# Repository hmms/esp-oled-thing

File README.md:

# esp-oled-thing
yet another esp8266 project

PCB designed in eagle 6.2.0.

gerbers in .zip file sent to OSH park 

this is still a work in progress.

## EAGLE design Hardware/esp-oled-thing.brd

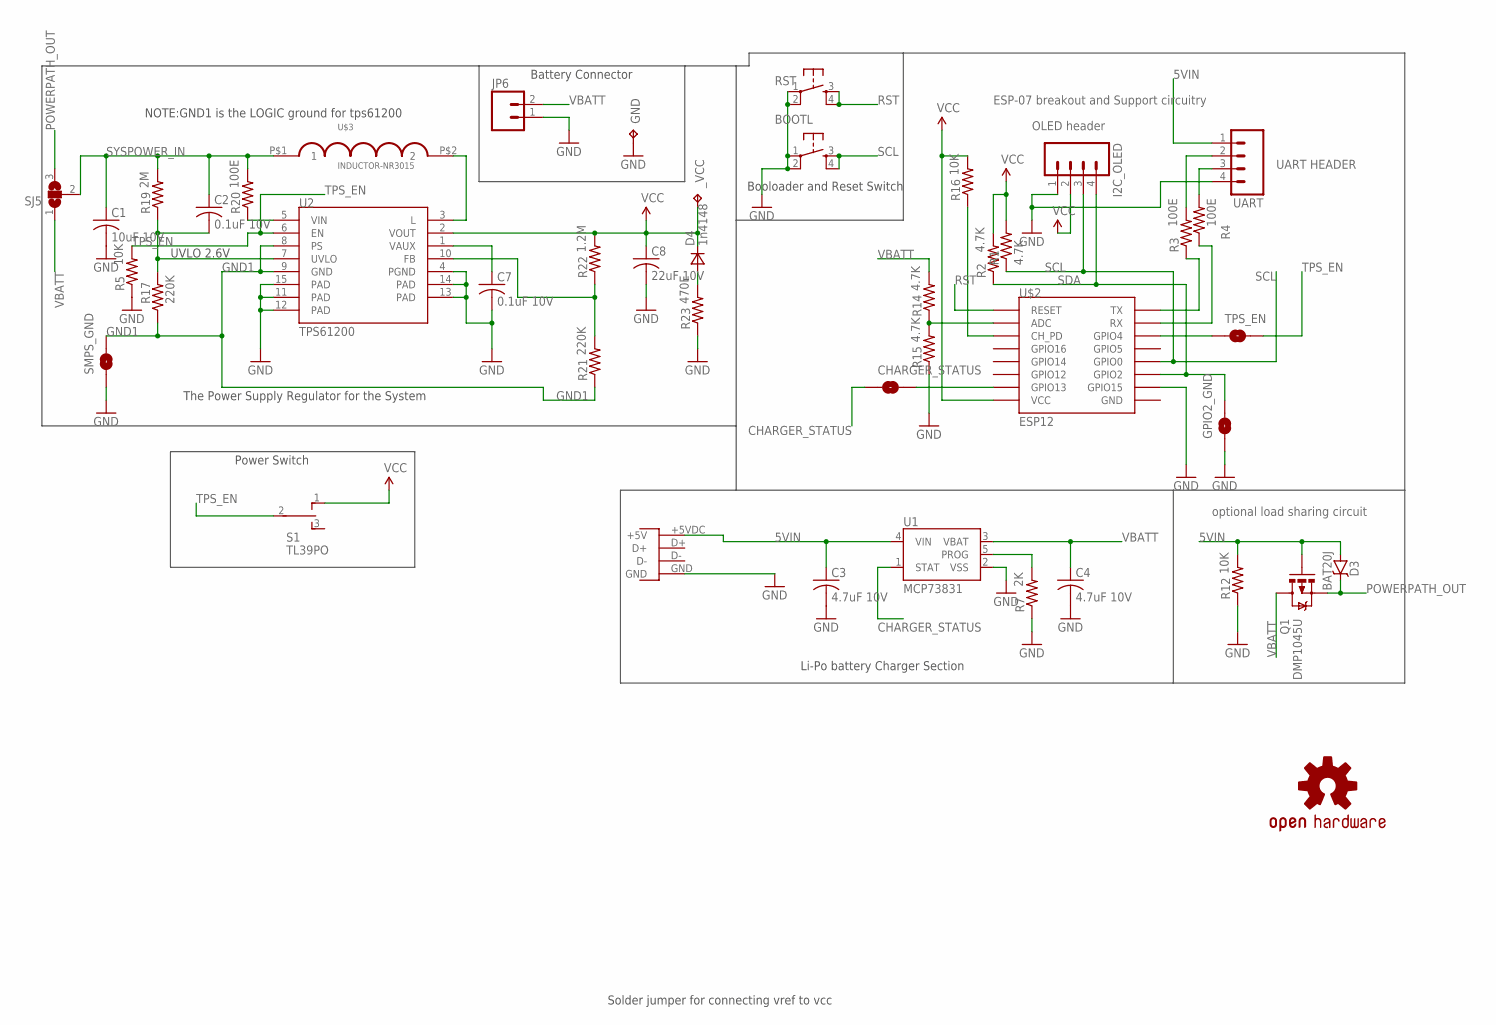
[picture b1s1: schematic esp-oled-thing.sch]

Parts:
BOOTL: TAC_SWITCHSMD; TACTILE_SWITCH_SMD
C1: 10uF 10V; C0805
C2, C7: 0.1uF 10V; C0805
C3, C4: 4.7uF 10V; C0805
C8: 22uF 10V; C0805
CHARGER_STATUS: SOLDERJUMPERNO; SJ_2S-NO
D3: BAT20J; SOD-323
D4: 1n4148; SOD323
GND: TPTP10R; TP10R
GPIO2_GND: SOLDERJUMPERNO; SJ_2S-NO
I2C_OLED: M04PTH; 1X04
JP6: M02JST-PTH-2; JST-2-PTH
Q1: DMP1045U; SOT23-3
R1, R2, R14, R15: 4.7K; M0805
R3, R4, R20: 100E; M0805
R5, R12, R16: 10K; M0805
R7: 2K; M0805
R17, R21: 220K; M0805
R19: 2M; M0805
R22: 1.2M; M0805
R23: 470E; M0805
RST: TAC_SWITCHSMD; TACTILE_SWITCH_SMD
S1: TL39PO; TL3XPO
SJ5: SJ2W; SJ_2
SMPS_GND: SOLDERJUMPERNO; SJ_2S-NO
TPS_EN: SOLDERJUMPERNO; SJ_2S-NO
U1: MCP73831; SOT23-5
U2: TPS61200; QFN-10_PAD
U$1: OSHW-LOGOS; OSHW-LOGO-S
U$2: ESP12
U$3: INDUCTOR-NR3015
U$4: MICROUSB-MIDMOUNT; MICROUSB-MIDMOUNT-MOLEX
UART: M04LONGPADS; 1X04_LONGPADS
_VCC: TPTP10R; TP10R

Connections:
5VIN: C3.1, D3.A, Q1.1 (G), R12.2, U1.4 (VIN), U$4.+5VDC (+5V), UART.1
CHARGER_STATUS: CHARGER_STATUS.1, U1.1 (STAT)
FB: R21.2, R22.1, U2.10 (FB)
GND: BOOTL.1, BOOTL.2, C1.2, C3.2, C4.2, C7.2, C8.2, GND.TP, GPIO2_GND.1, I2C_OLED.1, JP6.1, R5.1, R7.1, R12.1, R15.1, R23.1, RST.1, RST.2, SMPS_GND.1, U1.2 (VSS), U2.4 (PGND), U2.11 (PAD), U2.12 (PAD), U2.13 (PAD), U2.14 (PAD), U2.15 (PAD), U$2.GPIO15, U$4.GND, UART.4
GND1: R17.1, R21.1, SMPS_GND.2, U2.8 (PS), U2.9 (GND)
unnamed: CHARGER_STATUS.2, U$2.GPIO13
unnamed: R14.1, R15.2, U$2.ADC
unnamed: R16.1, U$2.CH_PD
unnamed: R3.2, UART.2
unnamed: TPS_EN.1, U$2.GPIO4
unnamed: R4.2, UART.3
unnamed: R7.2, U1.5 (PROG)
unnamed: U2.3 (L), U$3.P$2 (2)
unnamed: C7.1, U2.1 (VAUX)
unnamed: R3.1, U$2.TX
unnamed: R4.1, U$2.RX
unnamed: D4.2 (A), R23.2
POWERPATH_OUT: D3.C, Q1.2 (S), SJ5.3
RST: RST.3, RST.4, U$2.RESET
SCL: BOOTL.3, BOOTL.4, I2C_OLED.3, R1.1, U$2.GPIO0
SDA: GPIO2_GND.2, I2C_OLED.4, R2.1, U$2.GPIO2
SYSPOWER_IN: C1.1, C2.1, R19.2, R20.2, SJ5.2, U$3.P$1 (1)
TPS_EN: R5.2, S1.2, TPS_EN.2, U2.6 (EN)
UVLO: C2.2, R17.2, R19.1, U2.7 (UVLO)
VBATT: C4.1, JP6.2, Q1.3 (D), R14.2, SJ5.1, U1.3 (VBAT)
VCC: C8.1, D4.1 (C), I2C_OLED.2, R1.2, R2.2, R16.2, R22.2, S1.1 (O), U2.2 (VOUT), U$2.VCC, _VCC.TP
VIN: R20.1, U2.5 (VIN)

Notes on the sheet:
OLED header
UART HEADER
Booloader and Reset Switch
ESP-07 breakout and Support circuitry
UVLO 2.6V
NOTE:GND1 is the LOGIC ground for tps61200
Li-Po battery Charger Section
The Power Supply Regulator for the System
Solder jumper for connecting vref to vcc
optional load sharing circuit
Power Switch
Battery Connector

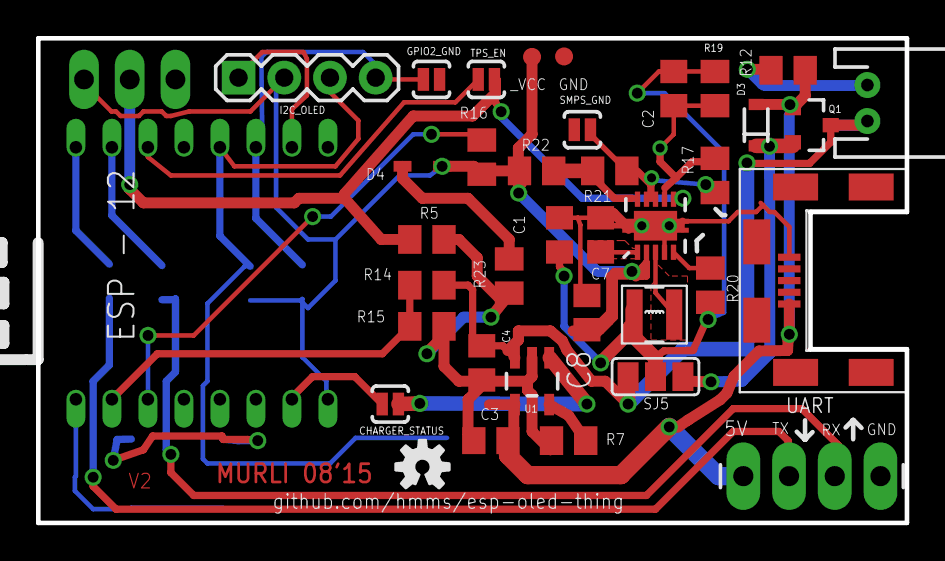
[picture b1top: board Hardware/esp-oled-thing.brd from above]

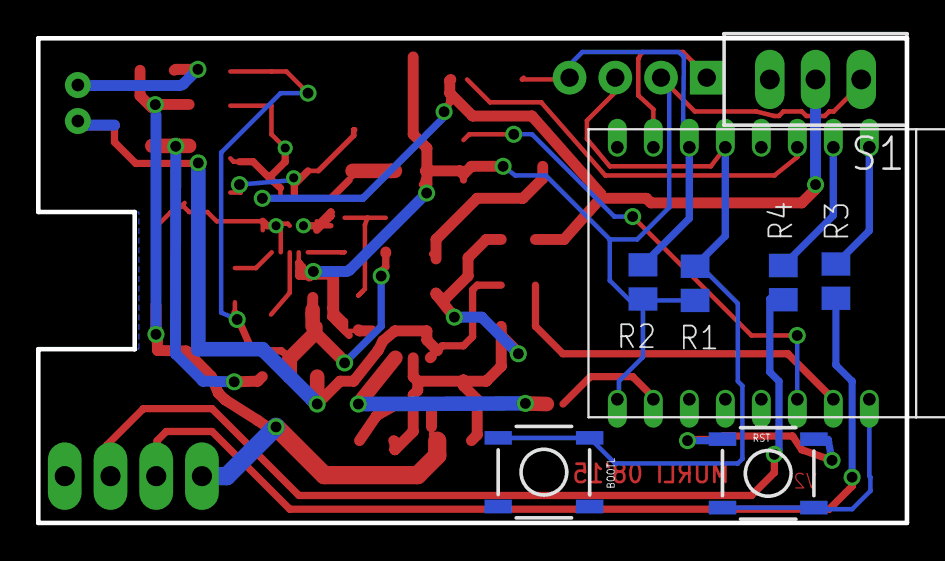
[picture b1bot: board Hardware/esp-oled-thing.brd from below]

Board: 2 copper layers, 48.3 x 26.9 mm, 44 parts (7 on the bottom side), 27 nets.

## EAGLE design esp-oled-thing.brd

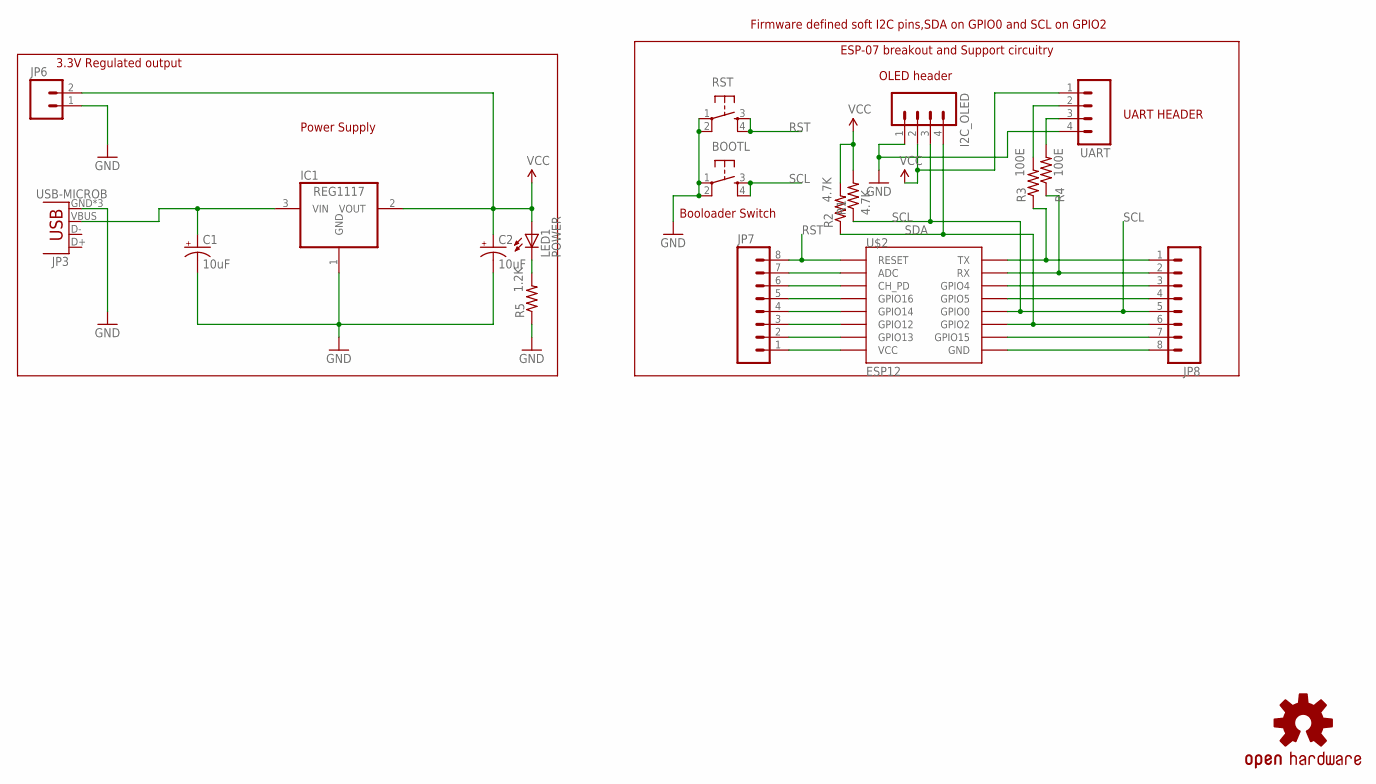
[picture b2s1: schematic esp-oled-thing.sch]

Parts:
BOOTL: TAC_SWITCHSMD; TACTILE_SWITCH_SMD
C1, C2: 10uF; EIA3216
I2C_OLED: M04PTH; 1X04
IC1: REG1117; SOT223
JP3: USB-MICROB
JP6: M02JST-PTH-2; JST-2-PTH
JP7, JP8: M081X08; 1X08
LED1: POWER; CHIPLED_0805
R1, R2: 4.7K; M0805
R3, R4: 100E; M0805
R5: 1.2K; M0805
RST: TAC_SWITCHSMD; TACTILE_SWITCH_SMD
U$1: OSHW-LOGOS; OSHW-LOGO-S
U$2: ESP12
UART: M04LONGPADS; 1X04_LONGPADS

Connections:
GND: BOOTL.1, BOOTL.2, C1.C (-), C2.C (-), I2C_OLED.1, IC1.1 (GND), JP3.GND, JP3.MT1 (GND), JP3.MT2 (GND), JP6.1, R5.1, RST.1, RST.2, UART.4
unnamed: C1.A (+), IC1.3 (VIN), JP3.VBUS
unnamed: JP7.1, U$2.VCC
unnamed: JP7.7, U$2.ADC
unnamed: R3.2, UART.2
unnamed: JP7.5, U$2.GPIO16
unnamed: JP7.4, U$2.GPIO14
unnamed: JP7.3, U$2.GPIO12
unnamed: R4.2, UART.3
unnamed: JP7.2, U$2.GPIO13
unnamed: LED1.C, R5.2
unnamed: JP8.3, U$2.GPIO4
unnamed: JP8.4, U$2.GPIO5
unnamed: JP8.7, U$2.GPIO15
unnamed: JP8.8, U$2.GND
unnamed: JP7.6, U$2.CH_PD
unnamed: JP8.1, R3.1, U$2.TX
unnamed: JP8.2, R4.1, U$2.RX
RST: JP7.8, RST.3, RST.4, U$2.RESET
SCL: BOOTL.3, BOOTL.4, I2C_OLED.3, JP8.5, R1.1, U$2.GPIO0
SDA: I2C_OLED.4, JP8.6, R2.1, U$2.GPIO2
VCC: C2.A (+), I2C_OLED.2, IC1.2 (VOUT), JP6.2, LED1.A, R1.2, R2.2, UART.1

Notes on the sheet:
OLED header
UART HEADER
Booloader Switch
Power Supply
ESP-07 breakout and Support circuitry
Firmware defined soft I2C pins,SDA on GPIO0 and SCL on GPIO2
3.3V Regulated output

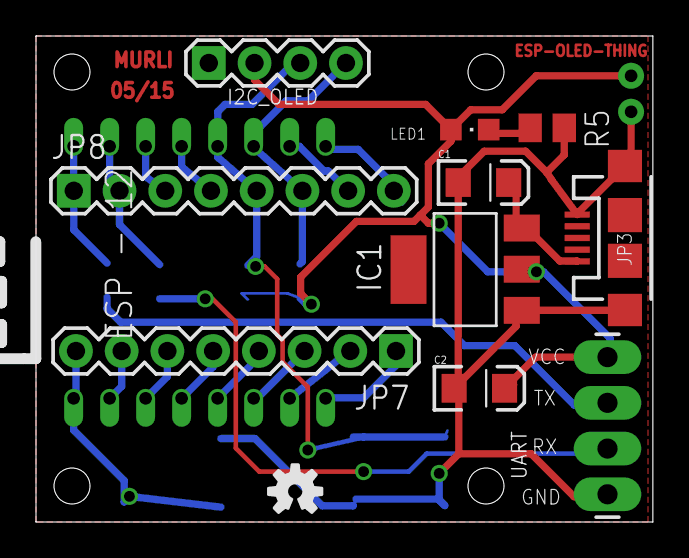
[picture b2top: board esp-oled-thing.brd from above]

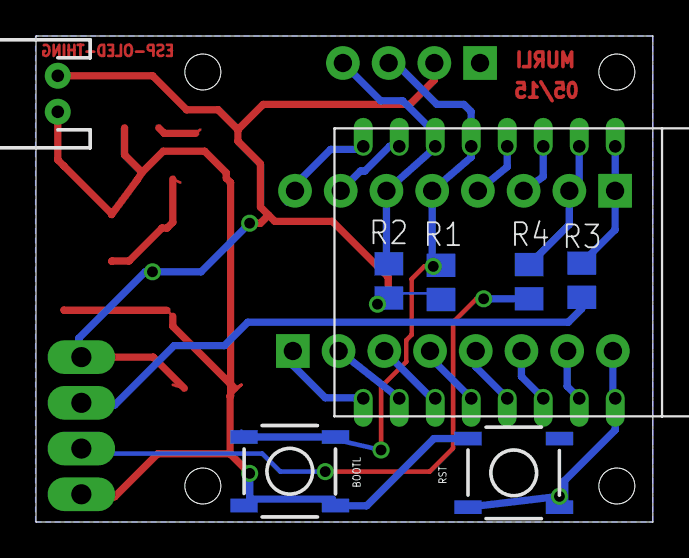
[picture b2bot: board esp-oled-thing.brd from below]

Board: 2 copper layers, 34.3 x 27.0 mm, 19 parts (7 on the bottom side), 22 nets.

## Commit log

2015-06-16 initial commit with all the pcb design files for esp-oled-thing
2015-06-16 readme updated
2015-06-18 tps61200 and mcp73831 for better lipo battery support added, usb connector changed to a more sturdier form factor
2015-06-18 hardware files movedd to hardware folder. basic firmware to test and validate the hardware to come soon.
2015-06-21 TPS61200 based system power, mc73831 lipo charger added. microusb changed to a sturdier design. some more minor bug fixes in the ESP-12 section. ability to control power (enable-disable the regulator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
2015-07-01 minor shchematic changes, initial board layout started.
2015-07-08 minor layout modifications
2015-07-08 more layout changes
2015-07-09 Initial layout started.
2015-07-10 power regulator layout done
2015-07-12 more layout progress
2015-07-12 more layout progress, some optimisation needed in the layout.
2015-07-22 layout and components modified for better solderability.
2015-07-24 Preliminary layout finished. Replaced passives with easier to solder 0805 parts. needs more optimization
2015-07-29 drc and cleanup in progress
2015-08-06 routing done. need to clean up the silkscreen. first commit from new lab (apartment?)
2015-08-20 silkscreen fixed, minor issues pending, will attempt to optimize the layout further.
2015-08-21 final DRC before sending it out. some errors fixed.
2015-08-25 'rev 2' hardware files sent to OSHPARK. NOT a final release, next release scheduled for end September with bug fixes - if any and aesthetic changes to fit in an enclosure.
2015-08-28 parts ordered from Digikey,BOM added. Change quantity before ordering.
2015-09-17 Firmware folder added
2015-10-04 serial print hello world, simple firmware test
2015-10-04 firmware put into the folder arduino style, serves a simple hello world webpage.

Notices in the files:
parts and their libraries:
SparkFun: Licensing: CC v3.0 Share-Alike You are welcome to use this library for commercial purposes.
SparkFun-DiscreteSemi: Licensing: Creative Commons ShareAlike 4.0 International - https://creativecommons.org/licenses/by-sa/4.0
